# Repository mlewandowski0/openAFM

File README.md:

# openAFM

for completion also is required : 
- stm32f373 dev board ( I used STM32F373C8T6 board). External DAC for next iterations for better performance is required ( STM32F373 has 16-bit ADC but 12-bit DAC)
- DDS module for preamplifer (I used AD9833 board, also tested AD9850, both works fine). Both are rather expensive IC's but cheap module can be found on aliexpress or equivalent ( they work reasonably well)
- CD4046 board for PLL ( currently on breadboard, design and PCB will be released )

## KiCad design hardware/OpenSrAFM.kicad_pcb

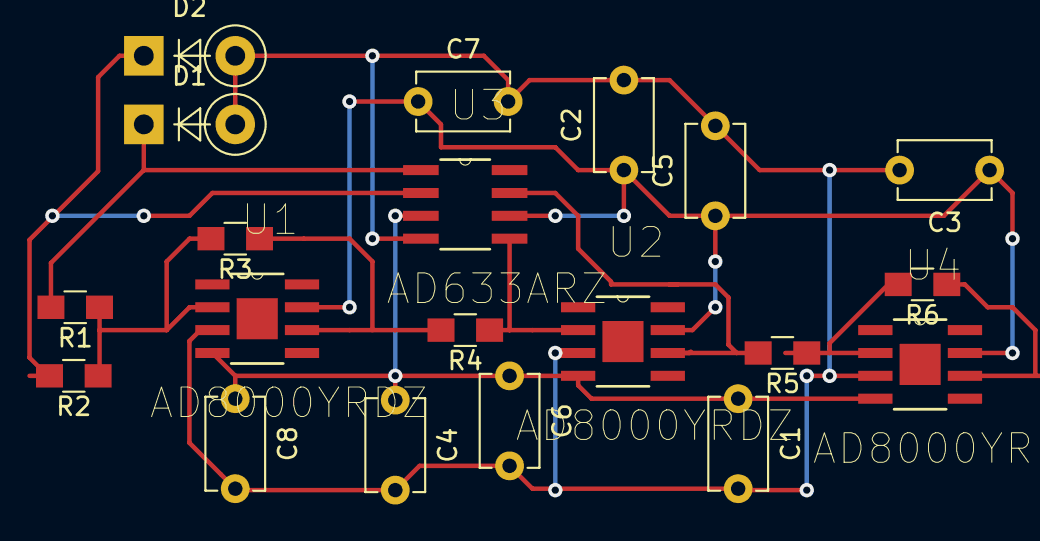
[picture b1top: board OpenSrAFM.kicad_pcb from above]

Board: 2 copper layers, 20 parts (0 on the bottom side), 11 nets.

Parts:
C1, C2, C3, C4, C5, C6, C7, C8: 100nF; C_Disc_D5.1mm_W3.2mm_P5.00mm
D1, D2: D_Photo; D_DO-41_SOD81_P5.08mm_Vertical_KathodeUp
R1, R2, R3, R4, R5, R6: 10k; R_0805_HandSoldering
U1, U2, U4: AD8000YRDZ; SOIC127P600X175-9N
U3: AD633ARZ; SOIC127P600X175-8N

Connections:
+15V: C2.1, C3.1, C5.1, C7.1, U1.7, U2.7, U3.6, U4.7
-15V: C1.1, C4.1, C6.1, C8.1, U1.4, U2.4, U3.3, U4.4
GNDREF: C1.2, C2.2, C3.2, C4.2, C5.2, C6.2, C7.2, C8.2, D1.2, D2.2, U1.3, U2.3, U3.4, U4.3
LINE: R6.1, U4.6
unnamed: D1.1, R1.2, U3.1
unnamed: D2.1, R2.2, U3.2
unnamed: R1.1, R2.1, R3.2, U1.2
unnamed: R3.1, R4.2, U1.6
unnamed: R4.1, U2.2, U3.5
unnamed: R5.1, R6.2, U4.2
unnamed: R5.2, U2.6, U3.7

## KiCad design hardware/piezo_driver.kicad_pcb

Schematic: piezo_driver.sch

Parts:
100k1, 100k2, 100k3, 100k4, 100k5, 100k6, 100k7, 100k8, 470k1, 470k2, 470k3, 470k4: R; R_Axial_DIN0204_L3.6mm_D1.6mm_P5.08mm_Horizontal
U1, U2, U3, U4, U5, U6: LM741; DIP-8_W7.62mm_Socket

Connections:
+15V: U1.7, U2.7, U3.7, U4.7, U5.7, U6.7
-15V: U1.4, U2.4, U3.4, U4.4, U5.4, U6.4
Earth: U1.3, U2.3, U3.3, U4.3, U5.3, U6.3
unnamed: 100k1.1, 470k1.2, U1.2
unnamed: 100k1.2, 100k2.2
unnamed: 100k2.1, 100k5.2, U2.2
unnamed: 100k3.1, 100k6.2, U3.2
unnamed: 100k3.2, 100k4.2
unnamed: 100k4.1, 470k2.2, U4.2
unnamed: 100k5.1, 100k7.2, U2.6
unnamed: 100k6.1, 100k8.2, U3.6
unnamed: 100k7.1, 470k3.2, U5.2
unnamed: 100k8.1, 470k4.2, U6.2
unnamed: 470k1.1, U1.6
unnamed: 470k2.1, U4.6
unnamed: 470k3.1, U5.6
unnamed: 470k4.1, U6.6

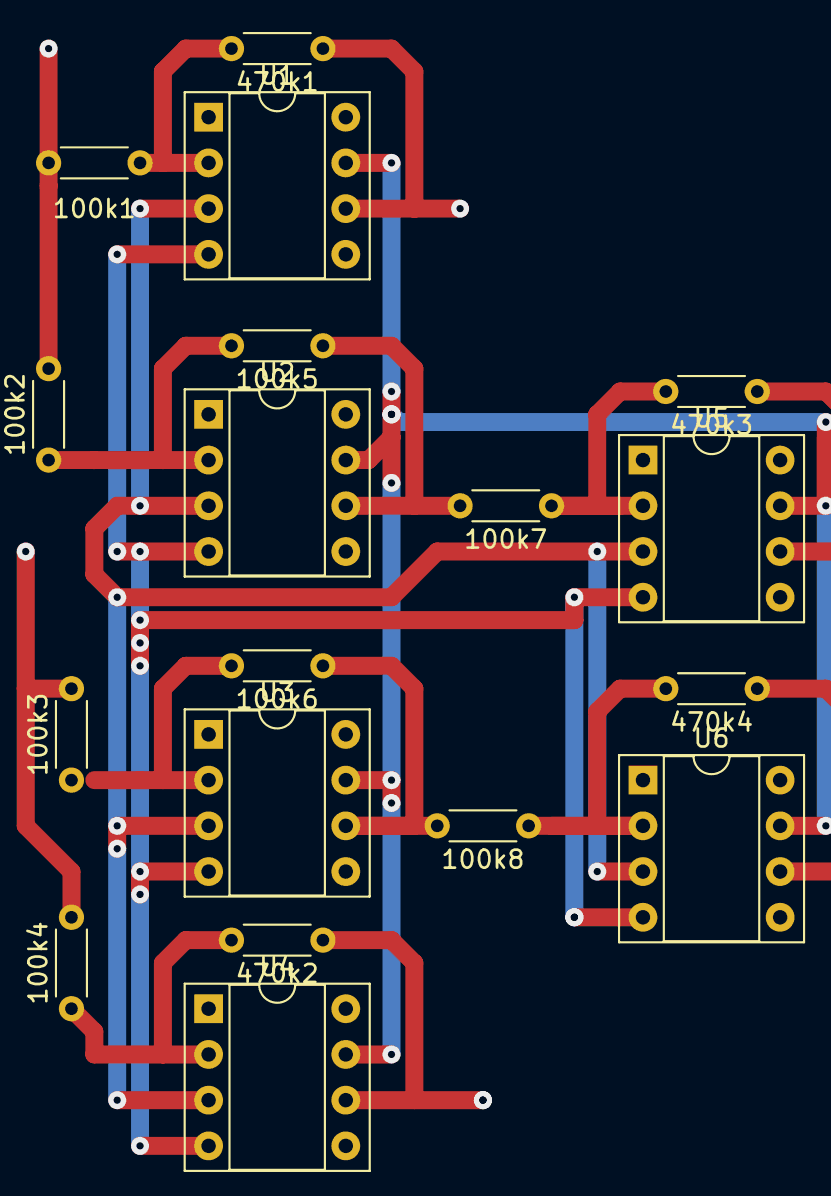
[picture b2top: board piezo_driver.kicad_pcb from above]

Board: 2 copper layers, 18 parts (0 on the bottom side), 17 nets.

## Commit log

2018-10-09 Add files via upload
    drivers schematics and photodiode schematics
2018-10-14 Schemat i pcb wzmacniacza do piezoelektryka. Niedokończony. Pogrubiam ścieżki
2018-10-14 Zmiana nazwy folderu z Wzmocnienie Piezzo/ na StackDriver. Pogrubione ścieżki 0.5mm i oddzielone 0.55. Schemat skończony
2018-10-14 Brzydko wyglądająca ścieżka przy wejściach: POPRAWIONA
2018-10-15 debug
2018-10-15 add pdf
2018-10-15 good pdf
2018-12-10 PSPD
2020-08-09 OPU, preamplifier for tuning fork, 3d designs, more will follow
